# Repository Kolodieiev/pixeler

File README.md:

<div align="center">

# 🎨 Pixeler

**Lightweight C++ GUI, Game & Firmware Framework for ESP32 / ESP32-S3 / ESP32-P4**  
*Швидкий фреймворк для розробки прошивок, графічних інтерфейсів та ігор під мікроконтролери ESP32*

[**🇬🇧 English**](#-english) | [**🇺🇦 Українська**](#-українська) | [**📚 Documentation / Документація**](docs/) | [**💻 PC Simulator (`pixeler4pc`)**](https://github.com/Kolodieiev/pixeler4pc)

---

### 📸 Showcase / Приклади інтерфейсів та застосунків

| Animated Menu UI | System Settings | Text Input & Virtual Keyboard |
| :---: | :---: | :---: |
|  |  |  |
| **Lua Scripting Context** | **2D RPG Game Engine Demo** | **Chess Game on ESP32-S3** |
|  |  |  |

</div>

---

## 🇬🇧 English

**Pixeler** is a modular C++ graphics, UI, and firmware framework designed for **ESP32**, **ESP32-S3**, and **ESP32-P4** microcontrollers. Instead of writing low-level boilerplate code for display rendering, screen transitions, file systems, and hardware inputs from scratch, Pixeler provides a ready-to-use application architecture inspired by Android's `Activity` lifecycle.

### ✨ Key Features

* **📱 Context-Based Architecture:** Manage applications, games, and screens using isolated Contexts (`IContext`) with automatic memory allocation and cleanup on transitions.
* **⚡ Rich UI Widgets & 2D Graphics:** Built on top of `Arduino_GFX`, offering ready-made UI widgets (menus, settings lists, textboxes with on-screen keyboards, dialogs) and smooth sprite rendering for 2D games (Chess, RPGs, etc.).
* **🌙 Lua Scripting Support:** Run dynamic user scripts and contexts powered by **Lua** without reflashing the microcontroller.
* **🖥️ Rapid Prototyping on PC ([pixeler4pc](https://github.com/Kolodieiev/pixeler4pc)):** Design, debug, and test your ESP32 graphical interfaces directly on your computer.
* **🎮 Unified Hardware Abstractions:** Out-of-the-box support for mechanical buttons, touchscreens, keyboards, I2C GPIO expanders, SD cards, and audio playback.
* **🤖 AI-Assisted Development Ready:** Includes [`AGENTS.md`](AGENTS.md) and structured documentation in [`docs/`](docs/) so AI coding assistants can generate valid Pixeler code immediately.

### 🛠️ Supported Hardware & Ecosystem

| Target / Project | Description | Link |
| :--- | :--- | :--- |
| **ESP32 / ESP32-S3 / ESP32-P4** | Core microcontroller families supported by Pixeler | [`src/`](src/) |
| **Perfect-Devboard** | Reference firmware & apps for Universal ESP32-S3 + CH32 board | [`examples/ESP32S3/Perfect-Devboard`](examples/ESP32S3/Perfect-Devboard) |
| **Lilka v2** | Alternative firmware built on Pixeler | [`examples/ESP32S3/Lilka_v2`](examples/ESP32S3/Lilka_v2) |
| **pixeler4pc** | Ported GUI engine for fast desktop UI development | [`Kolodieiev/pixeler4pc`](https://github.com/Kolodieiev/pixeler4pc) |

### 🚀 Quick Start (Pioarduino)

Add Pixeler to your `platformio.ini` or explore the ready-to-build firmware projects in [`examples/`](examples/):

```ini
lib_deps =
    [https://github.com/Kolodieiev/pixeler.git](https://github.com/Kolodieiev/pixeler.git)
```

Full setup instructions, driver configuration, and widget guides are available in the [**`docs/`**](docs/) directory.

---

## 🇺🇦 Українська

**Pixeler** — це модульний C++ фреймворк для швидкої розробки власних прошивок, графічних інтерфейсів (GUI) та 2D-ігор під мікроконтролери **ESP32**, **ESP32-S3** та **ESP32-P4**.

> **Готова архітектура замість рутини:** Pixeler бере на себе рендеринг графіки (`Arduino_GFX`), життєвий цикл екранів (за принципом Android `Activity`), віртуальну клавіатуру, роботу з SD-картою, звуком та вводом. Ви пишете лише логіку своїх застосунків або ігор.

### ✨ Основні можливості

* **📱 Система Контекстів (Contexts):** Кожен екран, гра або застосунок є ізольованим контекстом. Пам'ять виділяється лише під активний контекст і автоматично звільняється при перемиканні.
* **🧩 Віджети та ігрова графіка:** Готові компоненти інтерфейсу (анімовані меню, налаштування, текстові поля з клавіатурою, списки) та швидка робота зі спрайтами для 2D-ігор (шахи, RPG тощо).
* **🌙 Підтримка Lua:** Можливість виконання користувацьких Lua-скриптів та створення динамічних контекстів без перепрошивки плати.
* **💻 Симулятор для ПК ([pixeler4pc](https://github.com/Kolodieiev/pixeler4pc)):** Портована GUI-частина дозволяє верстати та тестувати інтерфейси прямо на комп'ютері за секунди.
* **🎛️ Робота з периферією:** Підтримка дисплеїв, тачскрінів, кнопок, I2C-експандерів, аудіо та SD-карт.
* **🤖 Підтримка AI-асистентів:** Файл [`AGENTS.md`](AGENTS.md) та документація в [`docs/`](docs/) дозволяють ШІ-агентам (Cursor, Copilot, Windsurf) миттєво генерувати валідний код під архітектуру Pixeler.

### 📂 З чого почати

1. **Перегляньте готові прошивки у [`examples/`](examples/):**
   * [**Perfect-Devboard**](examples/ESP32S3/Perfect-Devboard) — повноцінна прошивка з меню, налаштуваннями, Lua-контекстом та іграми для плати [perfect_devboard](https://github.com/Kolodieiev/perfect_devboard).
   * [**Lilka v2**](examples/ESP32S3/Lilka_v2) — порт прошивки під українську ретро-консоль Lilka v2.
2. **Ознайомтесь із документацією в [`docs/`](docs/):** покрокові інструкції з налаштування драйверів, створення власних контекстів та використання віджетів.
3. **Спробуйте розробку на ПК:** завантажте [**pixeler4pc**](https://github.com/Kolodieiev/pixeler4pc) для швидкого прототипування UI без заліза.

---

## ⭐️ Підтримка проєкту / Support

If **Pixeler** is useful for your ESP32 projects, please give this repository a **⭐️ Star**!  
Якщо проєкт став вам у пригоді — підтримайте репозиторій **⭐️ зірочкою**!

## 📄 License / Ліцензія

Licensed under the [**Apache License 2.0**](LICENSE).

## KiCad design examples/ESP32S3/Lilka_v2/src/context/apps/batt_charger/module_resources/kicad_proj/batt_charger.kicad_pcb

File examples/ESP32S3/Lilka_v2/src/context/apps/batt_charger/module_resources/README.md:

**Модуль заряду акумулятора**

Данний модуль та прошивку до нього розроблено для плати Lilka_v2.

Нижче наведено основні характеристики модуля за замовченням. 

* Підтримувані типи акумуляторів Li-ion/po, HV-Li-ion, LiFePo4.
* Напруга заряду: будь-яка в межах типу акумулятора.
* Струм заряду: 10мА-2А.

---

**Особливості збірки**

* На зображеннях модуль ADS не видно чітко, тому що він знаходиться під модулем INA. 
  Модулі з'єднанні етажеркою на звичайному гребінцю, тому що їх виводи живлення та I2C співпадають.
* На модулі DC-DC XL4016 земляний вхід та вихід повинні бути закорочені. Обмеженням струму керуватиме плата Лілки.
  Теоретично можна брати модуль без контролю струму, але такий варіант не тестувався. 
* Перед встановленням модуля DC-DC, потрібно виставити на ньому вихідну напругу 4.4В.

---

**Застереження та правила використання**

* Модуль не має надійного захисту від КЗ окрім як запобіжник, тому не нехтуйте його встановленням!
* В модулі відсутній захист від зворотньої напруги. Тому завжди приєднуйте акумулятор тільки після того, як переконаєтесь у коректності його полярності!
* Ніколи не залишайте модуль під час роботи без нагляду!
* За можливості заряджайте акумулятор через плату захисту!
* Ніколи не використовуйте модуль поряд з легкозаймистими матеріалами!

---

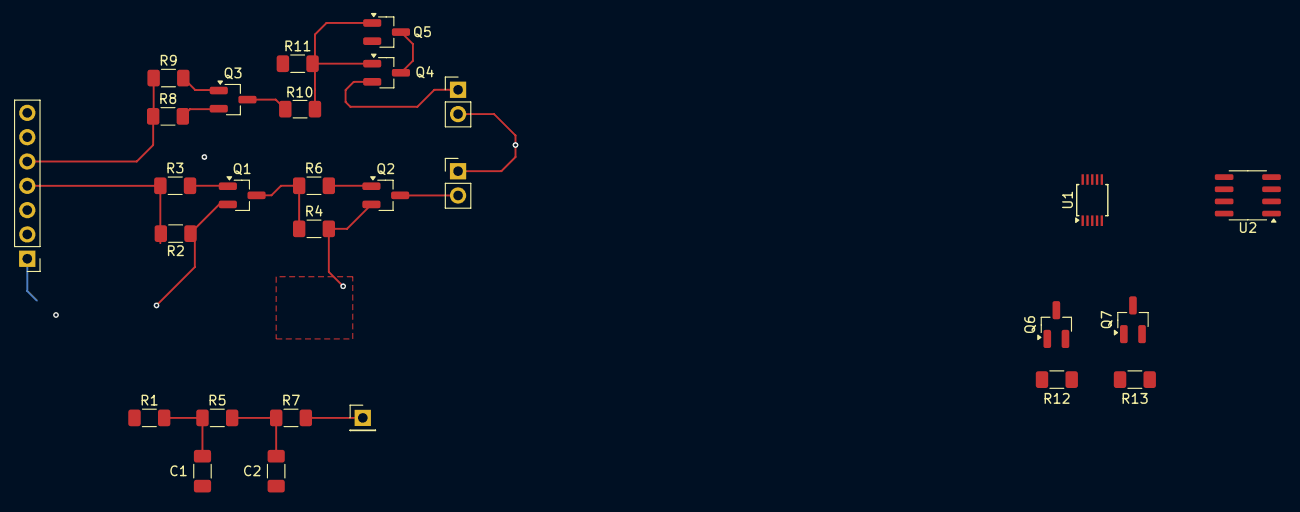
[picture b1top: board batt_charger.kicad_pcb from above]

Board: 2 copper layers, 28 parts (0 on the bottom side), 24 nets.

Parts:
C1, C2: 1uF; C_1206_3216Metric_Pad1.33x1.80mm_HandSolder
J1: Lilka_PINS; PinHeader_1x07_P2.54mm_Vertical
J2: XL4016_IN; PinHeader_1x02_P2.54mm_Vertical
J3: XL4016_FB; PinHeader_1x01_P2.54mm_Vertical
J4: XL4016_OUT; PinHeader_1x02_P2.54mm_Vertical
Q1, Q3, Q6, Q7: A09T; SOT-23_Handsoldering
Q2, Q4, Q5: A19T; SOT-23_Handsoldering
R1: 470; R_1206_3216Metric_Pad1.30x1.75mm_HandSolder
R2, R4, R8, R11: 20K; R_1206_3216Metric_Pad1.30x1.75mm_HandSolder
R3, R6, R9, R10: 100; R_1206_3216Metric_Pad1.30x1.75mm_HandSolder
R5, R7: 62; R_1206_3216Metric_Pad1.30x1.75mm_HandSolder
R12, R13: 5K; R_1206_3216Metric_Pad1.30x1.75mm_HandSolder
U1: ADS1115IDGS; TSSOP-10_3x3mm_P0.5mm
U2: INA219AxD; SOIC-8_3.9x4.9mm_P1.27mm

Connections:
3V3: J1.2, Q6.1 (G), Q7.1 (G), R12.1, R13.1
5V: Q2.2 (S), R4.2, R11.2, U1.8 (VDD), U2.5 (VS)
12: J1.3, R1.1
13: J1.4, R2.2, R3.1
14: J1.5, R8.1, R9.1
21: J1.6, Q6.2 (S), R12.2
47: J1.7, Q7.2 (S), R13.2
/V_IN+: J2.2, Q2.3 (D)
ADS_BAT_+: U1.4 (AIN0), U1.5 (AIN1), U2.7 (IN-)
ADS_DC_OUT: J4.1, Q4.2 (S), U1.6 (AIN2), U1.7 (AIN3)
GND: C1.2, C2.2, J1.1, J2.1, J4.2, Q1.2 (S), Q3.2 (S), R2.1, R8.2, U1.3 (GND), U2.6 (GND)
INA_IN+: Q5.2 (S), U2.8 (IN+)
unnamed: C1.1, R1.2, R5.1
unnamed: C2.1, R5.2, R7.1
unnamed: J3.1, R7.2
unnamed: Q1.3 (D), R4.1, R6.1
unnamed: Q1.1 (G), R3.2
unnamed: Q2.1 (G), R6.2
unnamed: Q3.3 (D), R10.2
unnamed: Q3.1 (G), R9.2
unnamed: Q4.3 (D), Q5.3 (D)
unnamed: Q4.1 (G), Q5.1 (G), R10.1, R11.1
unnamed: Q6.3 (D), U1.9 (SDA), U2.3 (SDA)
unnamed: Q7.3 (D), U1.10 (SCL), U2.4 (SCL)

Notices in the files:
README.md:
License: Apache 2.0
